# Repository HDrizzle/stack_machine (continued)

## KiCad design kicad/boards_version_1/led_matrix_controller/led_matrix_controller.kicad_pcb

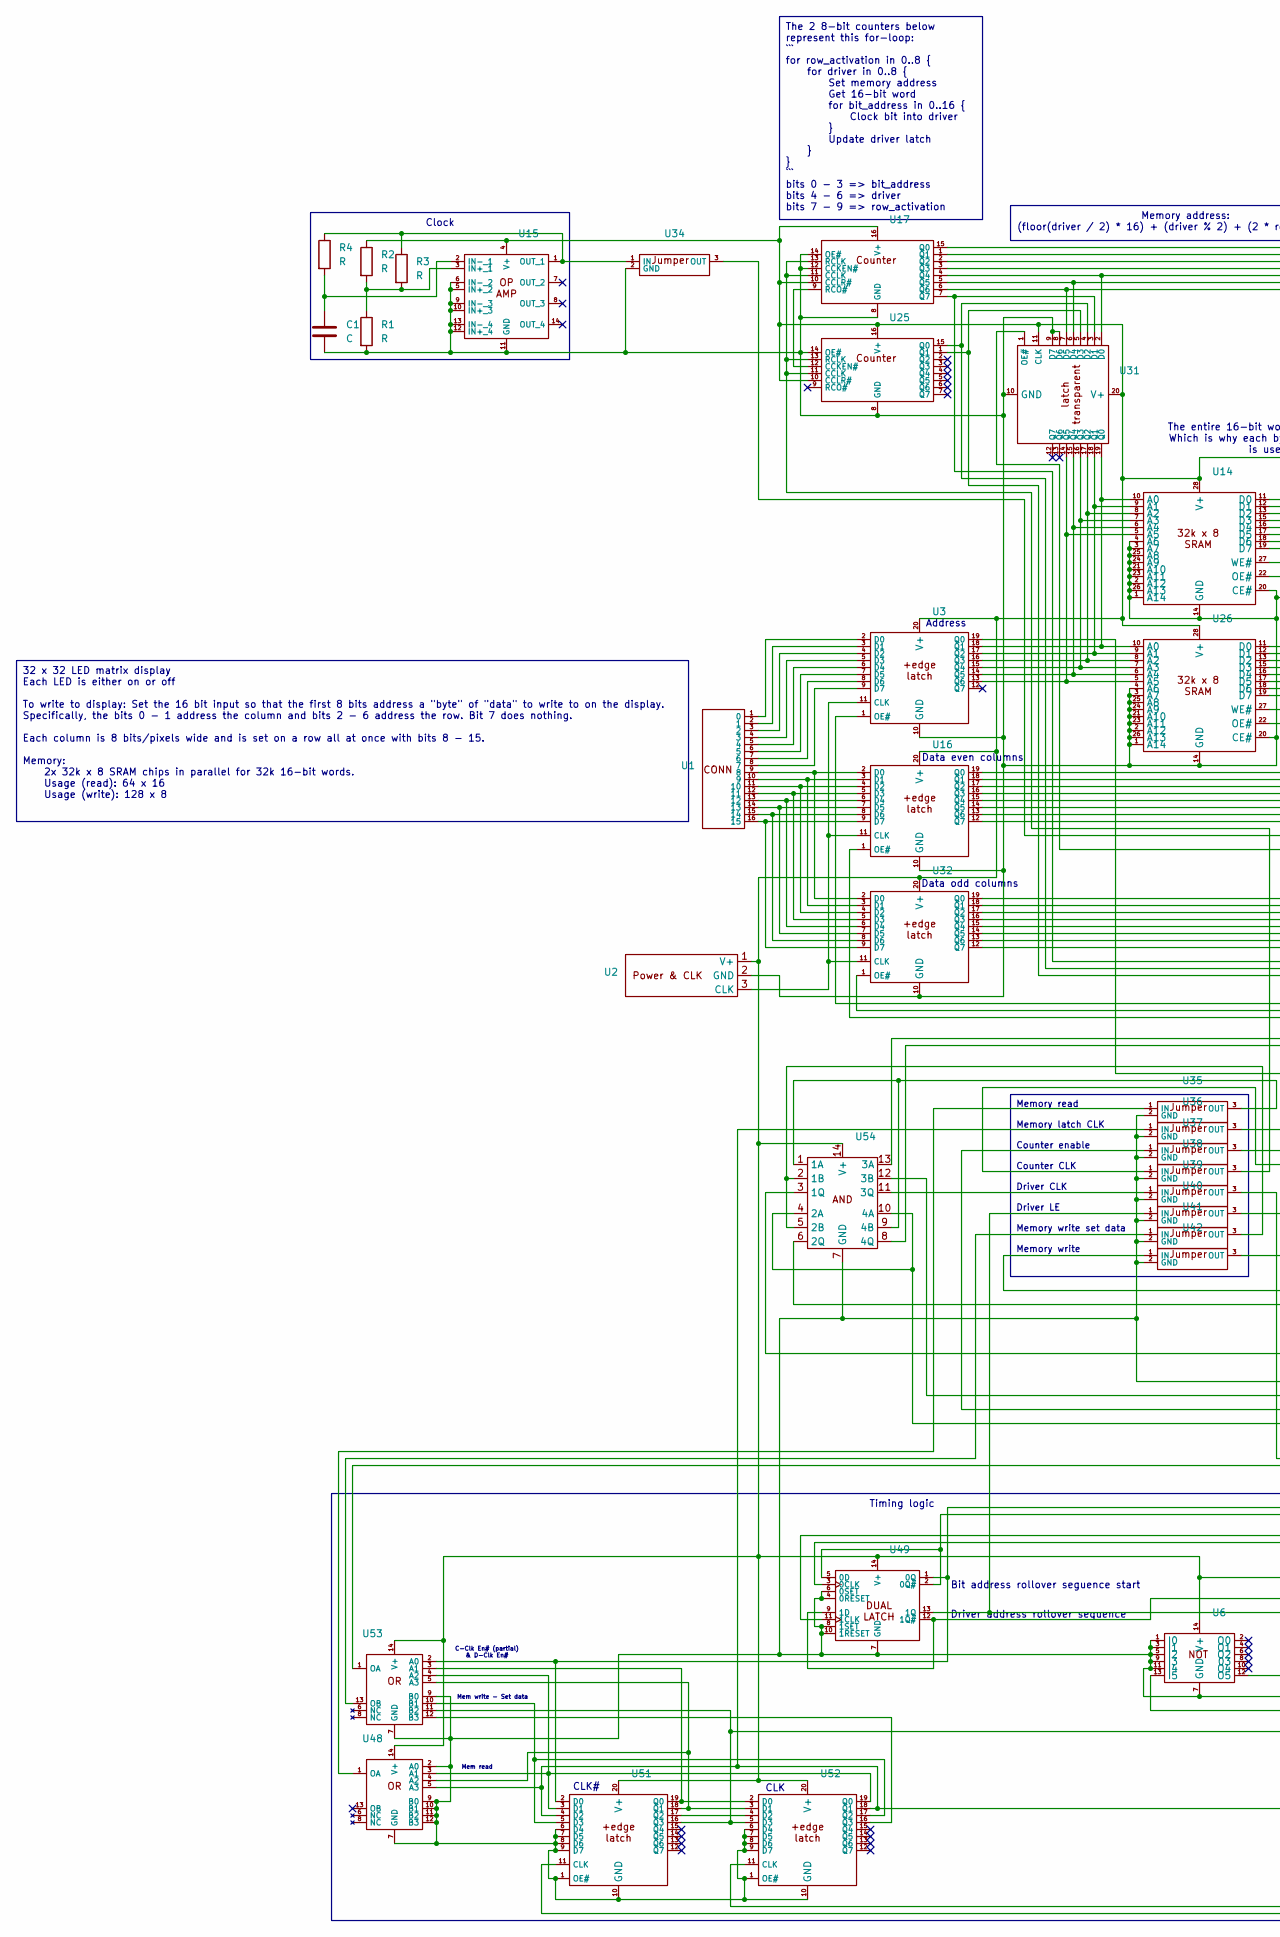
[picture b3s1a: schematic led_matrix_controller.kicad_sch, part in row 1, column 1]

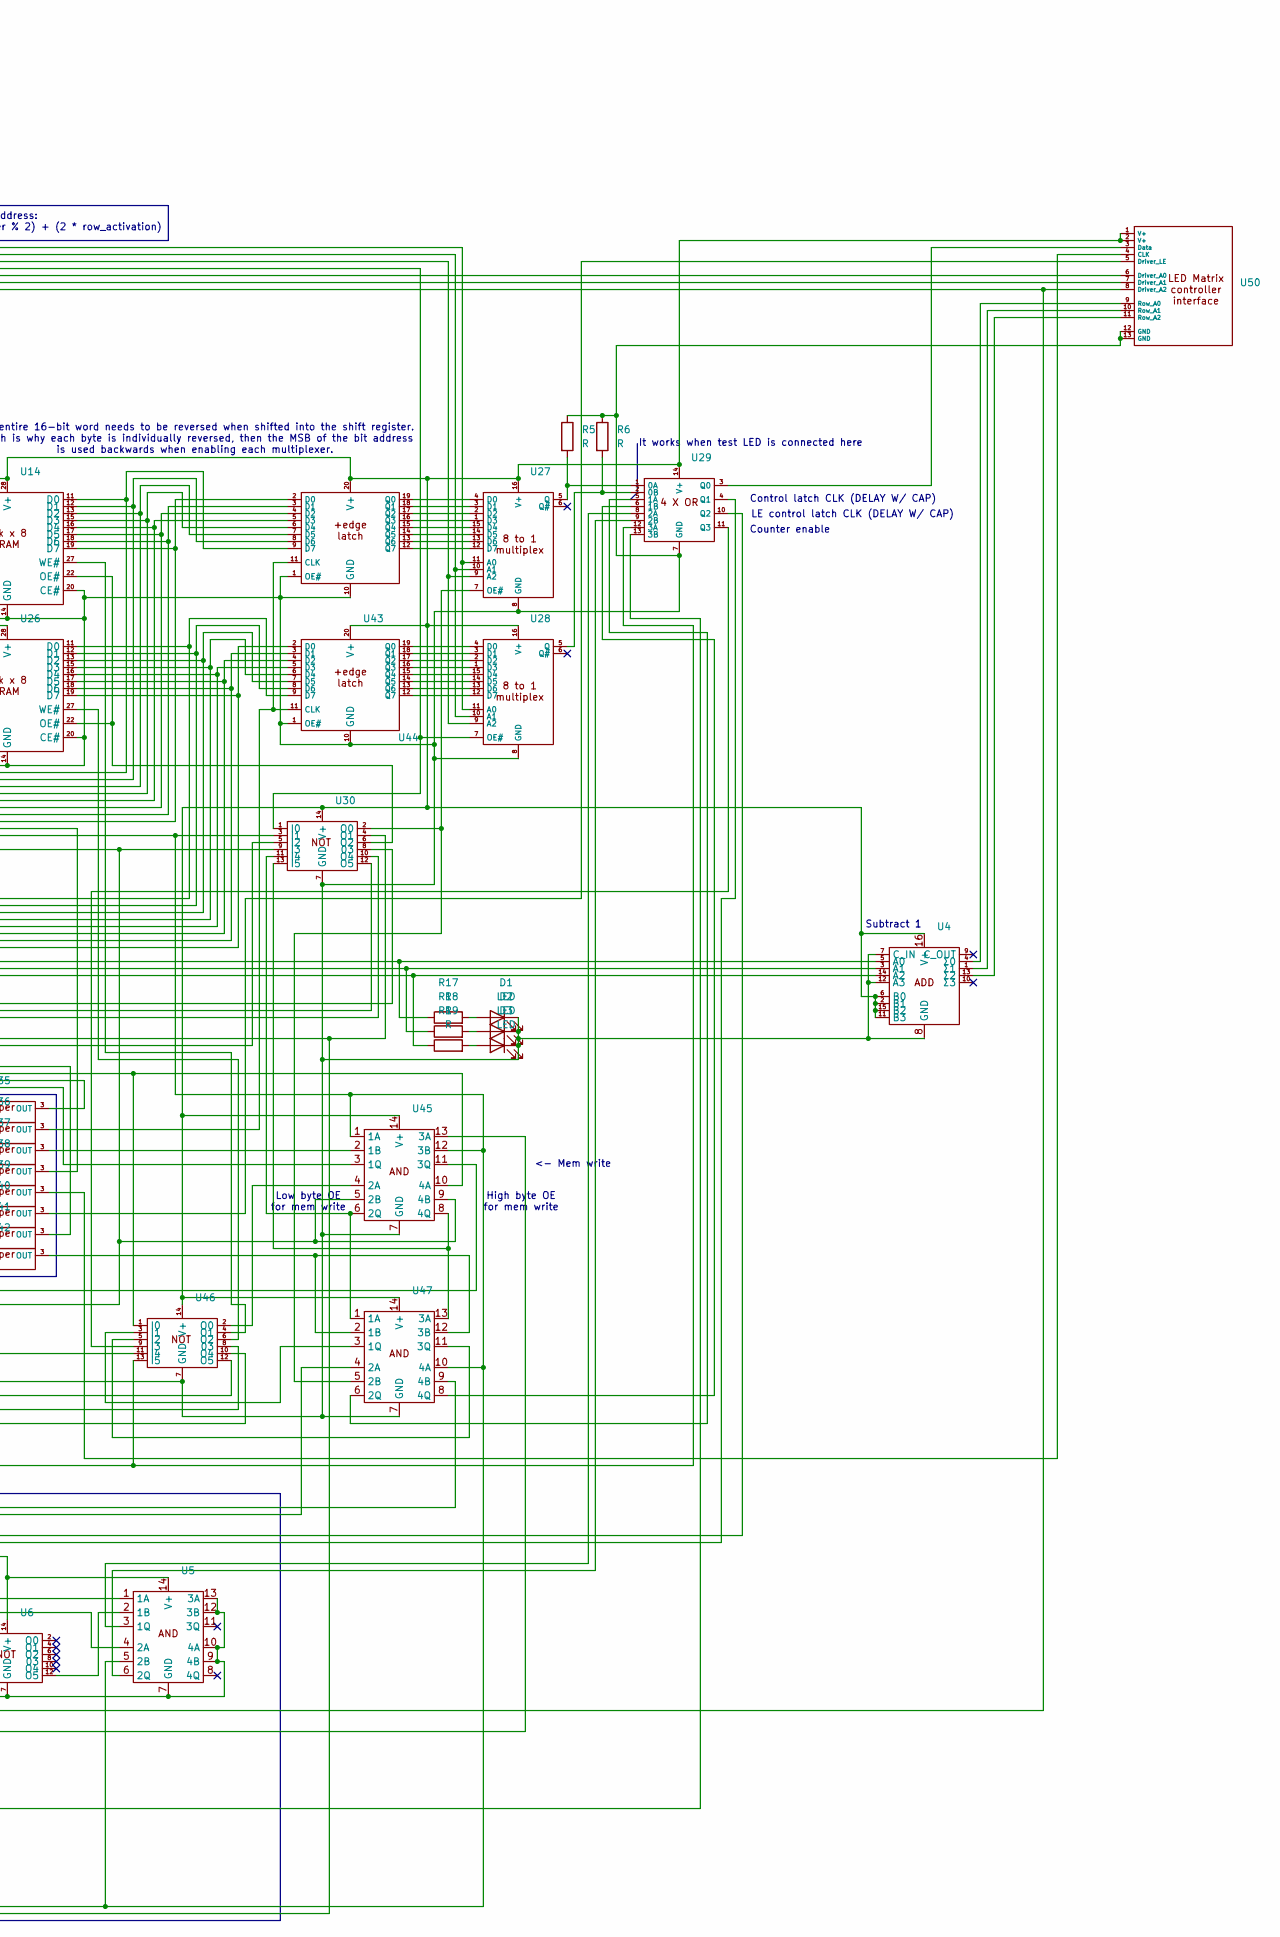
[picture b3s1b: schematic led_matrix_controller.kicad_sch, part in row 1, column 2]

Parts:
C1: C; CP_Radial_D4.0mm_P2.00mm
D1, D2, D3: LED; LED_D3.0mm
R1, R2, R3, R4, R5, R6, R17, R18, R19: R; 0.4_pitch_resistor
U1: PinHeader_1x16_P2.54mm_Vertical
U2: PinHeader_1x03_P2.54mm_Vertical
U3, U16, U31, U32, U43, U44, U51, U52: DIP-20_W7.62mm
U4, U17, U25, U27, U28: DIP-16_W7.62mm
U5, U6, U15, U29, U30, U45, U46, U47, U48, U49, U53, U54: DIP-14_W7.62mm
U14, U26: DIP-28_W15.24mm
U34, U35, U36, U37, U38, U39, U40, U41, U42: jumper
U50: PinHeader_1x13_P2.54mm_Vertical

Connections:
unnamed: D1.2 (A), R17.2
unnamed: C1.2, D1.1 (K), D2.1 (K), D3.1 (K), R1.2, R5.1, R6.1, U2.2 (GND), U3.10 (GND), U4.7 (C_IN), U4.8 (GND), U4.12 (A3), U5.7 (GND), U5.9 (4B), U5.10 (4A), U5.12 (3B), U5.13 (3A), U6.1 (I0), U6.3 (I1), U6.5 (I2), U6.7 (GND), U6.9 (I3), U6.11 (I4), U14.1 (A14), U14.2 (A12), U14.3 (A7), U14.4 (A6), U14.14 (GND), U14.20 (CE#), U14.21 (A10), U14.23 (A11), U14.24 (A9), U14.25 (A8), U14.26 (A13), U15.5 (IN+_2), U15.6 (IN-_2), U15.9 (IN-_3), U15.10 (IN+_3), U15.11 (GND), U15.12 (IN+_4), U15.13 (IN-_4), U16.10 (GND), U17.8 (GND), U17.12 (CCKEN#), U17.14 (OE#), U25.8 (GND), U25.14 (OE#), U26.1 (A14), U26.2 (A12), U26.3 (A7), U26.4 (A6), U26.14 (GND), U26.20 (CE#), U26.21 (A10), U26.23 (A11), U26.24 (A9), U26.25 (A8), U26.26 (A13), U27.8 (GND), U28.8 (GND), U29.7 (GND), U30.7 (GND), U31.8 (D6), U31.9 (D7), U31.10 (GND), U32.10 (GND), U34.2 (GND), U35.2 (GND), U36.2 (GND), U37.2 (GND), U38.2 (GND), U39.2 (GND), U40.2 (GND), U41.2 (GND), U42.2 (GND), U43.1 (OE#), U43.10 (GND), U44.1 (OE#), U44.10 (GND), U45.7 (GND), U46.7 (GND), U47.7 (GND), U48.2 (A0), U48.7 (GND), U48.9 (B0), U48.10 (B1), U48.11 (B2), U48.12 (B3), U49.4 (0RESET), U49.6 (0SET), U49.7 (GND), U49.8 (1SET), U49.10 (1RESET), U50.12 (GND), U50.13 (GND), U51.1 (OE#), U51.6 (D4), U51.7 (D5), U51.8 (D6), U51.9 (D7), U51.10 (GND), U52.1 (OE#), U52.6 (D4), U52.7 (D5), U52.8 (D6), U52.9 (D7), U52.10 (GND), U53.7 (GND), U53.9 (B0), U54.7 (GND)
unnamed: D2.2 (A), R18.2
unnamed: D3.2 (A), R19.2
unnamed: U1.1 (0), U3.2 (D0)
unnamed: U1.2 (1), U3.3 (D1)
unnamed: U1.3 (2), U3.4 (D2)
unnamed: U1.4 (3), U3.5 (D3)
unnamed: U1.5 (4), U3.6 (D4)
unnamed: U1.6 (5), U3.7 (D5)
unnamed: U1.7 (6), U3.8 (D6)
unnamed: U1.8 (7), U3.9 (D7)
unnamed: U1.9 (8), U16.2 (D0), U32.2 (D0)
unnamed: U1.10 (9), U16.3 (D1), U32.3 (D1)
unnamed: U1.11 (10), U16.4 (D2), U32.4 (D2)
unnamed: U1.12 (11), U16.5 (D3), U32.5 (D3)
unnamed: U1.13 (12), U16.6 (D4), U32.6 (D4)
unnamed: U1.14 (13), U16.7 (D5), U32.7 (D5)
unnamed: U1.15 (14), U16.8 (D6), U32.8 (D6)
unnamed: U1.16 (15), U16.9 (D7), U32.9 (D7)
unnamed: U3.1 (OE#), U30.8 (03)
unnamed: U3.19 (Q0), U45.10 (4A), U46.1 (I0)
unnamed: U4.4 (Σ0), U50.9 (Row_A0)
unnamed: U4.1 (Σ1), U50.10 (Row_A1)
unnamed: U4.13 (Σ2), U50.11 (Row_A2)
unnamed: U5.2 (1B), U6.12 (O5)
unnamed: U3.18 (Q1), U14.10 (A0), U26.10 (A0), U31.19 (Q0)
unnamed: U3.17 (Q2), U14.9 (A1), U26.9 (A1), U31.18 (Q1)
unnamed: U3.16 (Q3), U14.8 (A2), U26.8 (A2), U31.17 (Q2)
unnamed: U3.15 (Q4), U14.7 (A3), U26.7 (A3), U31.16 (Q3)
unnamed: U3.14 (Q5), U14.6 (A4), U26.6 (A4), U31.15 (Q4)
unnamed: U3.13 (Q6), U14.5 (A5), U26.5 (A5), U31.14 (Q5)
unnamed: U14.11 (D0), U16.19 (Q0), U44.9 (D7)
unnamed: U14.12 (D1), U16.18 (Q1), U44.8 (D6)
unnamed: U14.13 (D2), U16.17 (Q2), U44.7 (D5)
unnamed: U14.15 (D3), U16.16 (Q3), U44.6 (D4)
unnamed: U14.16 (D4), U16.15 (Q4), U44.5 (D3)
unnamed: U14.17 (D5), U16.14 (Q5), U44.4 (D2)
unnamed: U14.18 (D6), U16.13 (Q6), U44.3 (D1)
unnamed: U14.19 (D7), U16.12 (Q7), U44.2 (D0)
unnamed: U14.22 (OE#), U26.22 (OE#), U30.6 (O2)
unnamed: R2.1, U2.1 (V+), U3.20 (V+), U4.2 (B1), U4.6 (B0), U4.11 (B3), U4.15 (B2), U4.16 (V+), U5.14 (V+), U6.14 (V+), U14.28 (V+), U15.4 (V+), U16.20 (V+), U17.10 (CCLR#), U17.16 (V+), U25.10 (CCLR#), U25.16 (V+), U26.28 (V+), U27.16 (V+), U28.16 (V+), U29.14 (V+), U30.14 (V+), U31.11 (CLK), U31.20 (V+), U32.20 (V+), U43.20 (V+), U44.20 (V+), U45.14 (V+), U46.14 (V+), U47.14 (V+), U48.14 (V+), U49.14 (V+), U50.1 (V+), U50.2 (V+), U51.20 (V+), U52.20 (V+), U53.14 (V+), U54.14 (V+)
unnamed: U14.27 (WE#), U46.4 (O1)
unnamed: R1.1, R2.2, R3.2, U15.3 (IN+_1)
unnamed: C1.1, R4.2, U15.2 (IN-_1)
unnamed: R3.1, R4.1, U15.1 (OUT_1), U34.1 (IN)
unnamed: U2.3 (CLK), U3.11 (CLK), U16.11 (CLK), U32.11 (CLK)
unnamed: U16.1 (OE#), U30.10 (O4)
unnamed: U17.11 (CCLK), U17.13 (RCLK), U25.11 (CCLK), U25.13 (RCLK), U38.3 (OUT)
unnamed: U17.15 (Q0), U27.11 (A0), U28.11 (A0)
unnamed: U17.1 (Q1), U27.10 (A1), U28.10 (A1)
unnamed: U17.2 (Q2), U27.9 (A2), U28.9 (A2)
unnamed: U17.3 (Q3), U28.7 (OE#), U30.1 (I0)
unnamed: U17.4 (Q4), U31.2 (D0), U50.6 (Driver_A0)
unnamed: U17.5 (Q5), U31.6 (D4), U50.7 (Driver_A1)
unnamed: U6.13 (I5), U17.6 (Q6), U31.7 (D5), U50.8 (Driver_A2)
unnamed: R17.1, U4.5 (A0), U17.7 (Q7), U31.3 (D1)
unnamed: U17.9 (RCO#), U25.12 (CCKEN#)
unnamed: R18.1, U4.3 (A1), U25.15 (Q0), U31.4 (D2)
unnamed: R19.1, U4.14 (A2), U25.1 (Q1), U31.5 (D3)
unnamed: U26.11 (D0), U32.19 (Q0), U43.9 (D7)
unnamed: U26.12 (D1), U32.18 (Q1), U43.8 (D6)
unnamed: U26.13 (D2), U32.17 (Q2), U43.7 (D5)
unnamed: U26.15 (D3), U32.16 (Q3), U43.6 (D4)
unnamed: U26.16 (D4), U32.15 (Q4), U43.5 (D3)
unnamed: U26.17 (D5), U32.14 (Q5), U43.4 (D2)
unnamed: U26.18 (D6), U32.13 (Q6), U43.3 (D1)
unnamed: U26.19 (D7), U32.12 (Q7), U43.2 (D0)
unnamed: U26.27 (WE#), U46.6 (O2)
unnamed: U27.4 (D0), U44.19 (Q0)
unnamed: U27.3 (D1), U44.18 (Q1)
unnamed: U27.2 (D2), U44.17 (Q2)
unnamed: U27.1 (D3), U44.16 (Q3)
unnamed: U27.15 (D4), U44.15 (Q4)
unnamed: U27.14 (D5), U44.14 (Q5)
unnamed: U27.13 (D6), U44.13 (Q6)
unnamed: U27.12 (D7), U44.12 (Q7)
unnamed: U27.7 (OE#), U30.2 (O0), U47.5 (2B)
unnamed: R5.2, U27.5 (Q), U29.1 (0A)
unnamed: U28.4 (D0), U43.19 (Q0)
unnamed: U28.3 (D1), U43.18 (Q1)
unnamed: U28.2 (D2), U43.17 (Q2)
unnamed: U28.1 (D3), U43.16 (Q3)
unnamed: U28.15 (D4), U43.15 (Q4)
unnamed: U28.14 (D5), U43.14 (Q5)
unnamed: U28.13 (D6), U43.13 (Q6)
unnamed: U28.12 (D7), U43.12 (Q7)
unnamed: R6.2, U28.5 (Q), U29.2 (0B)
unnamed: U29.5 (1A), U47.6 (2Q)
unnamed: U29.6 (1B), U47.8 (4Q)
unnamed: U5.3 (1Q), U29.8 (2A)
unnamed: U5.6 (2Q), U29.9 (2B)
unnamed: U29.12 (3A), U46.13 (I5), U53.1 (OA)
unnamed: U29.13 (3B), U36.1 (IN), U48.5 (A3), U51.4 (D2), U52.18 (Q1)
unnamed: U29.3 (Q0), U50.3 (Data)
unnamed: U29.4 (Q1), U49.3 (0CLK)
unnamed: U29.10 (Q2), U49.11 (1CLK)
unnamed: U29.11 (Q3), U46.9 (I3)
unnamed: U5.5 (2B), U30.3 (I1), U34.3 (OUT), U45.1 (1A), U45.12 (3B), U47.10 (4A), U52.11 (CLK)
unnamed: U30.5 (I2), U54.8 (4Q)
unnamed: U30.9 (I3), U31.1 (OE#), U45.5 (2B), U45.9 (4B), U54.6 (2Q)
unnamed: U30.11 (I4), U45.6 (2Q), U47.1 (1A)
unnamed: U30.13 (I5), U45.8 (4Q), U47.13 (3A)
unnamed: U30.4 (O1), U51.11 (CLK), U54.13 (3A)
unnamed: U30.12 (O5), U32.1 (OE#)
unnamed: U35.1 (IN), U48.1 (OA)
unnamed: U35.3 (OUT), U54.1 (1A), U54.9 (4B)
unnamed: U36.3 (OUT), U43.11 (CLK), U44.11 (CLK)
unnamed: U37.1 (IN), U46.8 (03)
unnamed: U37.3 (OUT), U45.2 (1B)
unnamed: U38.1 (IN), U45.3 (1Q)
unnamed: U39.1 (IN), U54.11 (3Q)
unnamed: U39.3 (OUT), U50.4 (CLK)
unnamed: U5.4 (2A), U40.1 (IN), U49.13 (1Q)
unnamed: U40.3 (OUT), U50.5 (Driver_LE)
unnamed: U41.1 (IN), U53.13 (OB)
unnamed: U41.3 (OUT), U54.2 (1B), U54.5 (2B)
unnamed: U42.1 (IN), U45.11 (3Q)
unnamed: U42.3 (OUT), U47.2 (1B), U47.12 (3B)
unnamed: U45.4 (2A), U46.2 (O0)
unnamed: U45.13 (3A), U51.16 (Q3), U52.5 (D3), U53.11 (B2)
unnamed: U46.3 (I1), U47.3 (1Q)
unnamed: U46.5 (I2), U47.11 (3Q)
unnamed: U46.11 (I4), U54.3 (1Q)
unnamed: U46.10 (O4), U54.4 (2A), U54.10 (4A)
unnamed: U46.12 (O5), U54.12 (3B)
unnamed: U47.4 (2A), U49.2 (0Q#), U49.5 (0D)
unnamed: U47.9 (4B), U49.1 (0Q), U51.2 (D0), U53.2 (A0)
unnamed: U48.3 (A1), U51.3 (D1), U52.19 (Q0), U53.4 (A2)
unnamed: U48.4 (A2), U51.18 (Q1), U52.3 (D1), U53.5 (A3)
unnamed: U5.1 (1A), U49.9 (1D), U49.12 (1Q#)
unnamed: U51.5 (D3), U52.17 (Q2), U53.10 (B1)
unnamed: U51.19 (Q0), U52.2 (D0), U53.3 (A1)
unnamed: U51.17 (Q2), U52.4 (D2)
unnamed: U52.16 (Q3), U53.12 (B3)

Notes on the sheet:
Memory address: (floor(driver / 2) * 16) + (driver % 2) + (2 * row_activation)
The 2 8-bit counters below represent this for-loop: ``` for row_activation in 0..8 { for driver in 0..8 { Set memory address Get 16-bit word for bit_address in 0..16 { Clock bit into driver } Update driver latch } } ``` bits 0 - 3 => bit_address bits 4 - 6 => driver bits 7 - 9 => row_activation
32 x 32 LED matrix display Each LED is either on or off To write to display: Set the 16 bit input so that the first 8 bits address a "byte" of "data" to write to on the display. Specifically, the bits 0 - 1 address the column and bits 2 - 6 address the row. Bit 7 does nothing. Each column is 8 bits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
Memory read Memory latch CLK Counter enable Counter CLK Driver CLK Driver LE Memory write set data Memory write
Timing logic
Clock
Control latch CLK (DELAY W/ CAP)
Data even columns
Low byte OE for mem write
Address
<- Mem write
CLK
The entire 16-bit word needs to be reversed when shifted into the shift register. Which is why each byte is individually reversed, then the MSB of the bit address is used backwards when enabling each multiplexer.
Mem write - Set data
High byte OE for mem write
Mem read
C-Clk En# (partial) & D-Clk En#
Driver address rollover sequence
It works when test LED is connected here
Data odd columns
Bit address rollover seguence start
Counter enable
LE control latch CLK (DELAY W/ CAP)
Subtract 1
CLK#

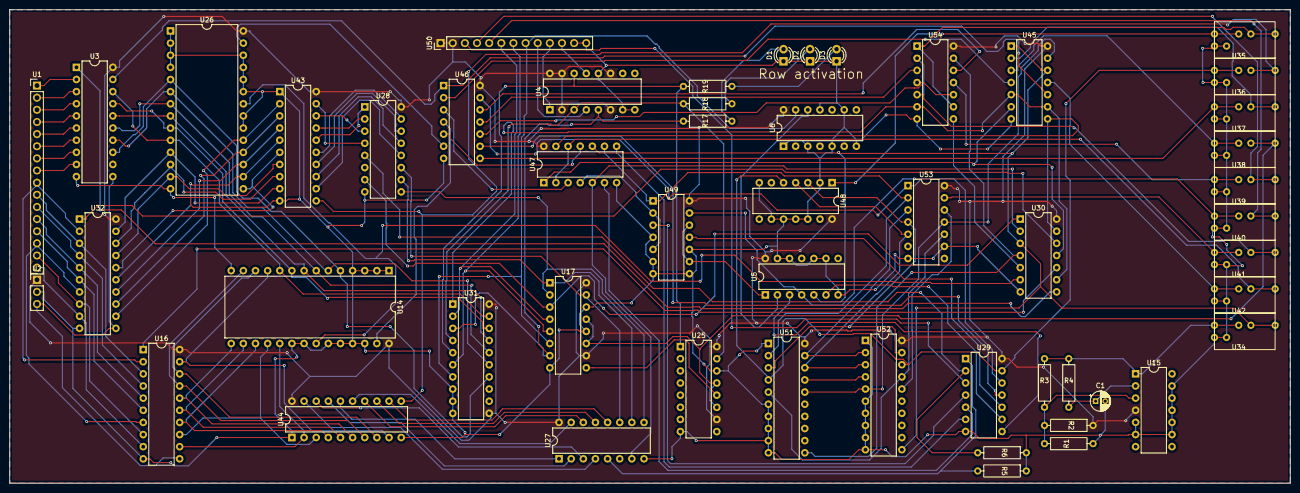
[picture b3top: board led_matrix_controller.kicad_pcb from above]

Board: 2 copper layers, 268.0 x 99.1 mm, 52 parts (0 on the bottom side), 135 nets.

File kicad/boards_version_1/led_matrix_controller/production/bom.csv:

Designator,Footprint,Quantity,Value,LCSC Part #
C1,CP_Radial_D4.0mm_P2.00mm,1,C,
"D1, D2, D3",LED_D3.0mm,3,LED,
"R1, R17, R18, R19, R2, R3, R4, R5, R6",0.4_pitch_resistor,9,R,
U1,PinHeader_1x16_P2.54mm_Vertical,1,~,
"U14, U26",DIP-28_W15.24mm,2,~,
"U15, U29, U30, U45, U46, U47, U48, U49, U5, U53, U54, U6",DIP-14_W7.62mm,12,~,
"U16, U3, U31, U32, U43, U44, U51, U52",DIP-20_W7.62mm,8,~,
"U17, U25, U27, U28, U4",DIP-16_W7.62mm,5,~,
U2,PinHeader_1x03_P2.54mm_Vertical,1,~,
"U34, U35, U36, U37, U38, U39, U40, U41, U42",jumper,9,~,
U50,PinHeader_1x13_P2.54mm_Vertical,1,~,

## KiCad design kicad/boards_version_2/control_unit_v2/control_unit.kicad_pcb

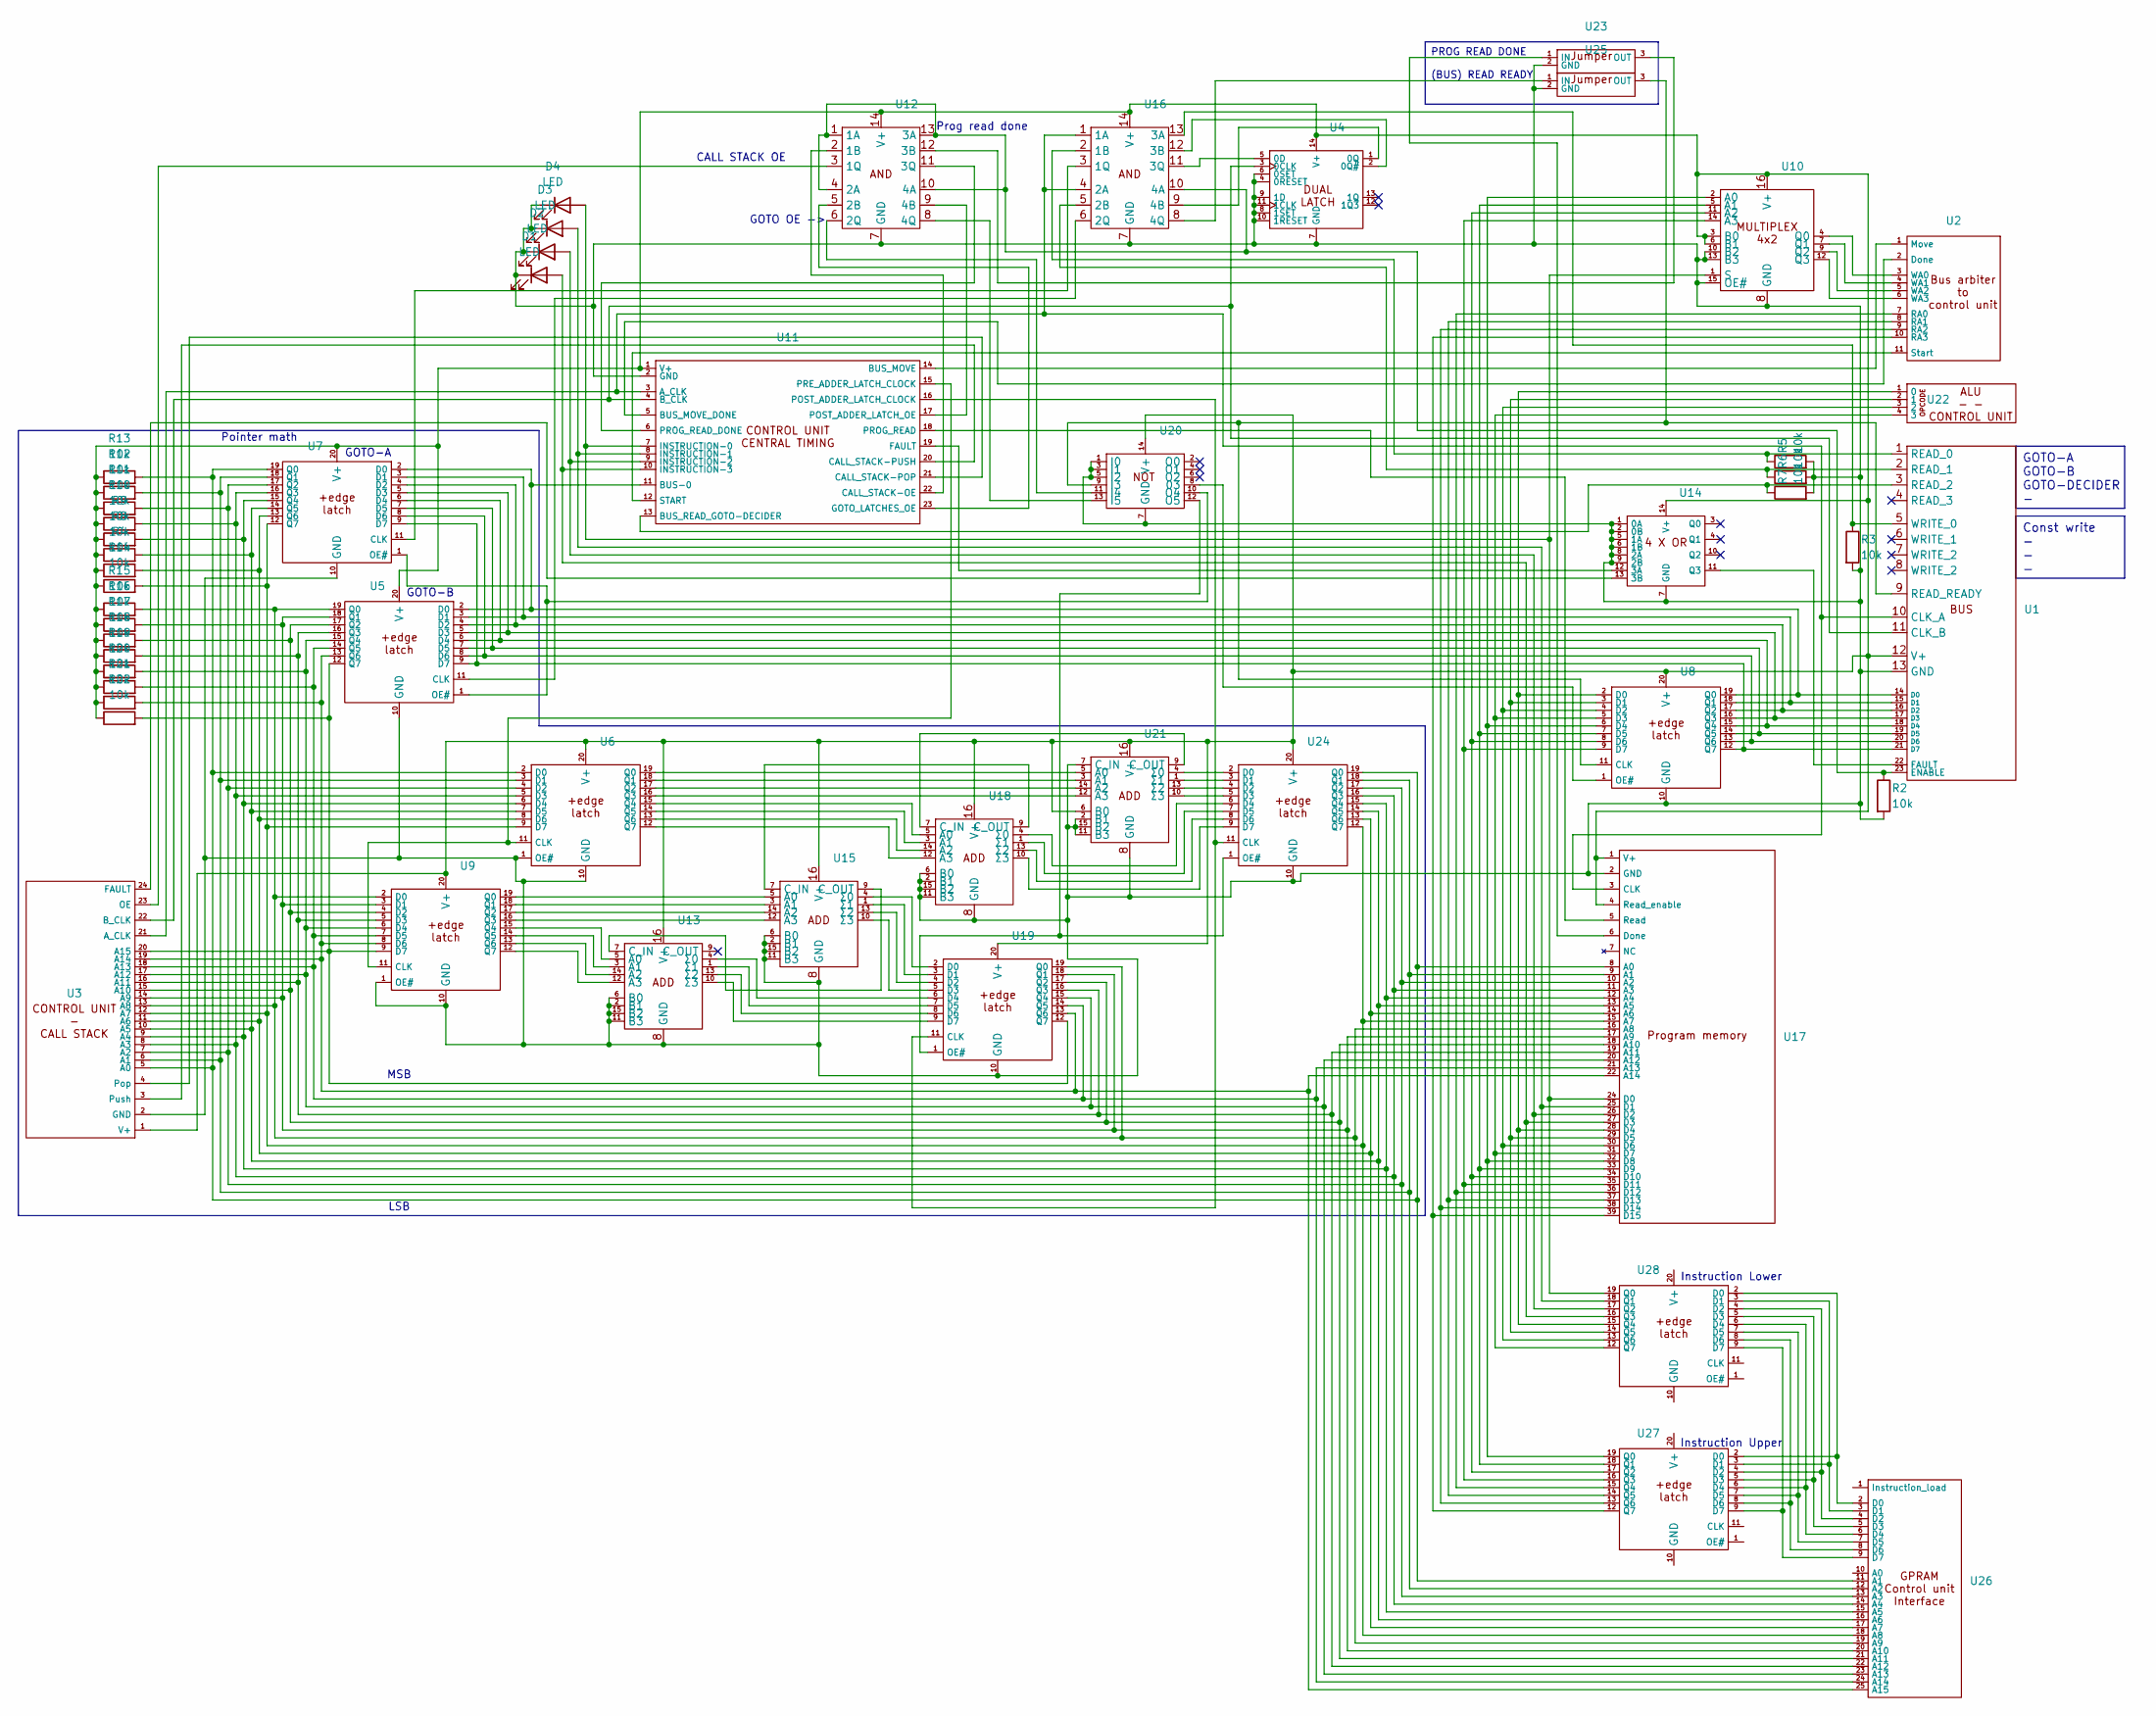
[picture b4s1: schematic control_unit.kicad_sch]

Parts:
D1, D2, D3, D4: LED; LED_D4.0mm
R2, R3, R4, R5, R6, R7, R8, R9, R10, R11, R12, R13, R14, R15, R16, R17, R18, R19, R20, R21, R22: 10k; 0.4_pitch_resistor
U1: PinHeader_1x23_P2.54mm_Vertical
U2: PinHeader_1x11_P2.54mm_Vertical
U3: PinHeader_1x24_P2.54mm_Vertical
U4, U12, U14, U16, U20: DIP-14_W7.62mm
U5, U6, U7, U8, U9, U19, U24, U27, U28: DIP-20_W7.62mm
U10, U13, U15, U18, U21: DIP-16_W7.62mm
U11: PinHeader_1x23_P2.54mm_Horizontal
U17: PinHeader_1x39_P2.54mm_Vertical
U22: PinHeader_1x04_P2.54mm_Vertical
U23, U25: jumper
U26: PinHeader_1x25_P2.54mm_Vertical

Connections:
unnamed: D1.2 (A), U11.10 (INSTRUCTION-3), U17.27 (D3), U28.16 (Q3)
unnamed: D1.1 (K), D2.1 (K), D3.1 (K), D4.1 (K), R2.2, R3.2, R5.2, R6.2, R7.2, U1.13 (GND), U3.2 (GND), U4.4 (0RESET), U4.6 (0SET), U4.7 (GND), U4.8 (1SET), U4.9 (1D), U4.10 (1RESET), U4.11 (1CLK), U5.10 (GND), U6.1 (OE#), U6.10 (GND), U7.10 (GND), U8.10 (GND), U9.1 (OE#), U9.10 (GND), U10.8 (GND), U10.10 (B2), U10.13 (B3), U10.15 (OE#), U11.2 (GND), U12.7 (GND), U13.2 (B1), U13.6 (B0), U13.8 (GND), U13.11 (B3), U13.15 (B2), U14.1 (0A), U14.2 (0B), U14.5 (1A), U14.6 (1B), U14.7 (GND), U14.8 (2A), U14.9 (2B), U15.2 (B1), U15.6 (B0), U15.8 (GND), U15.11 (B3), U15.15 (B2), U16.7 (GND), U17.2 (GND), U18.2 (B1), U18.6 (B0), U18.8 (GND), U18.11 (B3), U18.15 (B2), U19.10 (GND), U20.1 (I0), U20.3 (I1), U20.5 (I2), U20.7 (GND), U21.2 (B1), U21.7 (C_IN), U21.8 (GND), U21.11 (B3), U21.15 (B2), U23.2 (GND), U24.10 (GND), U25.2 (GND)
unnamed: D2.2 (A), U11.9 (INSTRUCTION-2), U17.26 (D2), U28.17 (Q2)
unnamed: D3.2 (A), U11.8 (INSTRUCTION-1), U17.25 (D1), U28.18 (Q1)
unnamed: D4.2 (A), U10.1 (S), U11.7 (INSTRUCTION-0), U17.24 (D0), U28.19 (Q0)
unnamed: U1.10 (CLK_A), U3.21 (A_CLK), U11.3 (A_CLK), U16.1 (1A), U16.4 (2A), U17.3 (CLK)
unnamed: U1.11 (CLK_B), U3.22 (B_CLK), U4.3 (0CLK), U11.4 (B_CLK)
unnamed: U1.14 (D0), U5.2 (D0), U7.2 (D0), U8.19 (Q0), U11.11 (BUS-0)
unnamed: U1.15 (D1), U5.3 (D1), U7.3 (D1), U8.18 (Q1)
unnamed: U1.16 (D2), U5.4 (D2), U7.4 (D2), U8.17 (Q2)
unnamed: U1.17 (D3), U5.5 (D3), U7.5 (D3), U8.16 (Q3)
unnamed: U1.18 (D4), U5.6 (D4), U7.6 (D4), U8.15 (Q4)
unnamed: U1.19 (D5), U5.7 (D5), U7.7 (D5), U8.14 (Q5)
unnamed: U1.20 (D6), U5.8 (D6), U7.8 (D6), U8.13 (Q6)
unnamed: U1.21 (D7), U5.9 (D7), U7.9 (D7), U8.12 (Q7)
unnamed: R2.1, U1.23 (ENABLE), U12.1 (1A), U12.4 (2A), U12.10 (4A), U12.13 (3A), U16.10 (4A)
unnamed: U1.22 (FAULT), U14.11 (Q3)
unnamed: R5.1, U1.1 (READ_0), U16.2 (1B)
unnamed: R6.1, U1.2 (READ_1), U16.5 (2B)
unnamed: R7.1, U1.3 (READ_2), U11.13 (BUS_READ_GOTO-DECIDER)
unnamed: U1.9 (READ_READY), U8.11 (CLK), U20.9 (I3), U25.3 (OUT)
unnamed: R4.1, R8.1, R9.1, R10.1, R11.1, R12.1, R13.1, R14.1, R15.1, R16.1, R17.1, R18.1, R19.1, R20.1, R21.1, R22.1, U1.12 (V+), U3.1 (V+), U4.14 (V+), U5.20 (V+), U6.20 (V+), U7.20 (V+), U8.20 (V+), U9.20 (V+), U10.3 (B0), U10.6 (B1), U10.16 (V+), U11.1 (V+), U12.14 (V+), U13.16 (V+), U14.14 (V+), U15.16 (V+), U16.14 (V+), U17.1 (V+), U17.4 (Read_enable), U18.16 (V+), U19.20 (V+), U20.14 (V+), U21.6 (B0), U21.16 (V+), U24.20 (V+)
unnamed: R3.1, U1.5 (WRITE_0), U16.13 (3A)
unnamed: U8.6 (D4), U10.2 (A0), U17.32 (D8), U27.19 (Q0)
unnamed: U8.7 (D5), U10.5 (A1), U17.33 (D9), U27.18 (Q1)
unnamed: U8.8 (D6), U10.11 (A2), U17.34 (D10), U27.17 (Q2)
unnamed: U8.9 (D7), U10.14 (A3), U17.35 (D11), U27.16 (Q3)
unnamed: U2.3 (WA0), U10.4 (Q0)
unnamed: U2.4 (WA1), U10.7 (Q1)
unnamed: U2.5 (WA2), U10.9 (Q2)
unnamed: U2.6 (WA3), U10.12 (Q3)
unnamed: U2.1 (Move), U11.14 (BUS_MOVE)
unnamed: U2.2 (Done), U11.5 (BUS_MOVE_DONE)
unnamed: U11.22 (CALL_STACK-OE), U12.2 (1B)
unnamed: U3.4 (Pop), U11.21 (CALL_STACK-POP)
unnamed: U3.3 (Push), U11.20 (CALL_STACK-PUSH)
unnamed: U11.19 (FAULT), U14.12 (3A)
unnamed: U11.23 (GOTO_LATCHES_OE), U12.5 (2B)
unnamed: U11.16 (POST_ADDER_LATCH_CLOCK), U19.11 (CLK), U24.11 (CLK)
unnamed: U11.17 (POST_ADDER_LATCH_OE), U12.9 (4B)
unnamed: U6.11 (CLK), U9.11 (CLK), U11.15 (PRE_ADDER_LATCH_CLOCK)
unnamed: U11.18 (PROG_READ), U17.5 (Read)
unnamed: U11.6 (PROG_READ_DONE), U12.11 (3Q)
unnamed: U2.11 (Start), U11.12 (START)
unnamed: U3.23 (OE), U12.3 (1Q)
unnamed: U12.6 (2Q), U20.11 (I4)
unnamed: U12.12 (3B), U23.3 (OUT)
unnamed: U12.8 (4Q), U20.13 (I5)
unnamed: U9.15 (Q4), U13.5 (A0)
unnamed: U9.14 (Q5), U13.3 (A1)
unnamed: U9.13 (Q6), U13.14 (A2)
unnamed: U9.12 (Q7), U13.12 (A3)
unnamed: U13.7 (C_IN), U15.9 (C_OUT)
unnamed: U13.4 (Σ0), U19.6 (D4)
unnamed: U13.1 (Σ1), U19.7 (D5)
unnamed: U13.13 (Σ2), U19.8 (D6)
unnamed: U13.10 (Σ3), U19.9 (D7)
unnamed: U3.24 (FAULT), U14.13 (3B)
unnamed: U9.19 (Q0), U15.5 (A0)
unnamed: U9.18 (Q1), U15.3 (A1)
unnamed: U9.17 (Q2), U15.14 (A2)
unnamed: U9.16 (Q3), U15.12 (A3)
unnamed: U15.7 (C_IN), U18.9 (C_OUT)
unnamed: U15.4 (Σ0), U19.2 (D0)
unnamed: U15.1 (Σ1), U19.3 (D1)
unnamed: U15.13 (Σ2), U19.4 (D2)
unnamed: U15.10 (Σ3), U19.5 (D3)
unnamed: U7.11 (CLK), U16.3 (1Q)
unnamed: U5.11 (CLK), U16.6 (2Q)
unnamed: U4.2 (0Q#), U16.12 (3B)
unnamed: U4.5 (0D), U16.11 (3Q)
unnamed: U4.1 (0Q), U16.9 (4B)
unnamed: U16.8 (4Q), U25.1 (IN)
unnamed: R13.2, U3.5 (A0), U6.2 (D0), U7.19 (Q0), U17.8 (A0), U24.19 (Q0), U26.11 (A1)
unnamed: R12.2, U3.6 (A1), U6.3 (D1), U7.18 (Q1), U17.9 (A1), U24.18 (Q1), U26.12 (A2)
unnamed: R11.2, U3.7 (A2), U6.4 (D2), U7.17 (Q2), U17.10 (A2), U24.17 (Q2), U26.13 (A3)
unnamed: R10.2, U3.8 (A3), U6.5 (D3), U7.16 (Q3), U17.11 (A3), U24.16 (Q3), U26.14 (A4)
unnamed: R9.2, U3.9 (A4), U6.6 (D4), U7.15 (Q4), U17.12 (A4), U24.15 (Q4), U26.15 (A5)
unnamed: R8.2, U3.10 (A5), U6.7 (D5), U7.14 (Q5), U17.13 (A5), U24.14 (Q5), U26.16 (A6)
unnamed: R4.2, U3.11 (A6), U6.8 (D6), U7.13 (Q6), U17.14 (A6), U24.13 (Q6), U26.17 (A7)
unnamed: R14.2, U3.12 (A7), U6.9 (D7), U7.12 (Q7), U17.15 (A7), U24.12 (Q7), U26.18 (A8)
unnamed: R15.2, U3.13 (A8), U5.19 (Q0), U9.2 (D0), U17.16 (A8), U19.19 (Q0), U26.19 (A9)
unnamed: R16.2, U3.14 (A9), U5.18 (Q1), U9.3 (D1), U17.17 (A9), U19.18 (Q1), U26.20 (A10)
unnamed: R17.2, U3.15 (A10), U5.17 (Q2), U9.4 (D2), U17.18 (A10), U19.17 (Q2), U26.21 (A11)
unnamed: R18.2, U3.16 (A11), U5.16 (Q3), U9.5 (D3), U17.19 (A11), U19.16 (Q3), U26.22 (A12)
unnamed: R19.2, U3.17 (A12), U5.15 (Q4), U9.6 (D4), U17.20 (A12), U19.15 (Q4), U26.23 (A13)
unnamed: R20.2, U3.18 (A13), U5.14 (Q5), U9.7 (D5), U17.21 (A13), U19.14 (Q5), U26.24 (A14)
unnamed: R21.2, U3.19 (A14), U5.13 (Q6), U9.8 (D6), U17.22 (A14), U19.13 (Q6), U26.25 (A15)
unnamed: R22.2, U3.20 (A15), U5.12 (Q7), U9.9 (D7), U17.23 (A15), U19.12 (Q7)
unnamed: U8.2 (D0), U17.28 (D4), U22.1 (0), U28.15 (Q4)
unnamed: U8.3 (D1), U17.29 (D5), U22.2 (1), U28.14 (Q5)
unnamed: U8.4 (D2), U17.30 (D6), U22.3 (2), U28.13 (Q6)
unnamed: U8.5 (D3), U17.31 (D7), U22.4 (3), U28.12 (Q7)
unnamed: U2.7 (RA0), U17.36 (D12), U27.15 (Q4)
unnamed: U2.8 (RA1), U17.37 (D13), U27.14 (Q5)
unnamed: U2.9 (RA2), U17.38 (D14), U27.13 (Q6)
unnamed: U2.10 (RA3), U17.39 (D15), U27.12 (Q7)
unnamed: U17.6 (Done), U23.1 (IN)
unnamed: U6.15 (Q4), U18.5 (A0)
unnamed: U6.14 (Q5), U18.3 (A1)
unnamed: U6.13 (Q6), U18.14 (A2)
unnamed: U6.12 (Q7), U18.12 (A3)
unnamed: U18.7 (C_IN), U21.9 (C_OUT)
unnamed: U18.4 (Σ0), U24.6 (D4)
unnamed: U18.1 (Σ1), U24.7 (D5)
unnamed: U18.13 (Σ2), U24.8 (D6)
unnamed: U18.10 (Σ3), U24.9 (D7)
unnamed: U19.1 (OE#), U20.12 (O5), U24.1 (OE#)
unnamed: U8.1 (OE#), U20.8 (03)
unnamed: U5.1 (OE#), U7.1 (OE#), U20.10 (O4)
unnamed: U6.19 (Q0), U21.5 (A0)
unnamed: U6.18 (Q1), U21.3 (A1)
unnamed: U6.17 (Q2), U21.14 (A2)
unnamed: U6.16 (Q3), U21.12 (A3)
unnamed: U21.4 (Σ0), U24.2 (D0)
unnamed: U21.1 (Σ1), U24.3 (D1)
unnamed: U21.13 (Σ2), U24.4 (D2)
unnamed: U21.10 (Σ3), U24.5 (D3)
unnamed: U26.2 (D0), U27.2 (D0), U28.2 (D0)
unnamed: U26.3 (D1), U27.3 (D1), U28.3 (D1)
unnamed: U26.4 (D2), U27.4 (D2), U28.4 (D2)
unnamed: U26.5 (D3), U27.5 (D3), U28.5 (D3)
unnamed: U26.6 (D4), U27.6 (D4), U28.6 (D4)
unnamed: U26.7 (D5), U27.7 (D5), U28.7 (D5)
unnamed: U26.8 (D6), U27.8 (D6), U28.8 (D6)
unnamed: U26.9 (D7), U27.9 (D7), U28.9 (D7)

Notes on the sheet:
GOTO OE ->
Instruction Upper
MSB
Instruction Lower
CALL STACK OE
GOTO-B
LSB
Prog read done
Pointer math
GOTO-A
GOTO-A GOTO-B GOTO-DECIDER -
PROG READ DONE (BUS) READ READY
Const write - - -

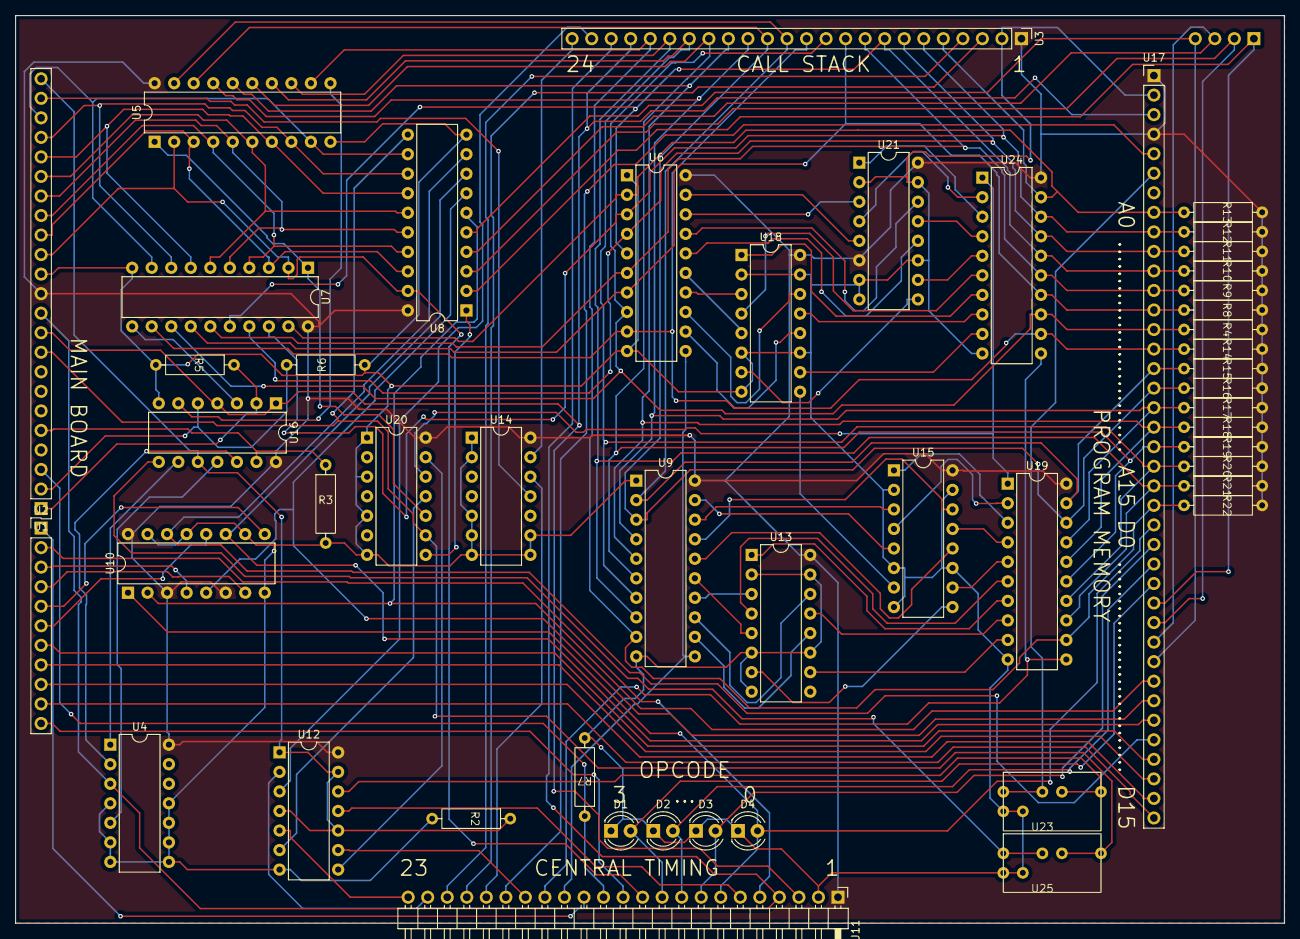
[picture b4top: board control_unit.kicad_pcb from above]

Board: 2 copper layers, 165.0 x 118.0 mm, 50 parts (1 on the bottom side), 118 nets.
